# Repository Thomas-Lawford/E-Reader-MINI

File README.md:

Solar Powered E-Reader Keychain 

Has a custom E-Paper driver circuit MicroSD card interface and solar energy harvesting circuit.

Based on the STM32U073 with sub 1 μW operational power consumption.

Has a custom FILEX implementation that supports EXfat and fat32 file systems (Supports SDUC, SDXC and SDHC), 3d printed Case design and a custom EPD lookup table for the 1.22 inch E paper display.

Power consumption is so low this design is battery free with a supercap to store charge for brief current spikes from microSD card reads.
 
 You can select a text file to read, jump to a specific page, and adjust the font size

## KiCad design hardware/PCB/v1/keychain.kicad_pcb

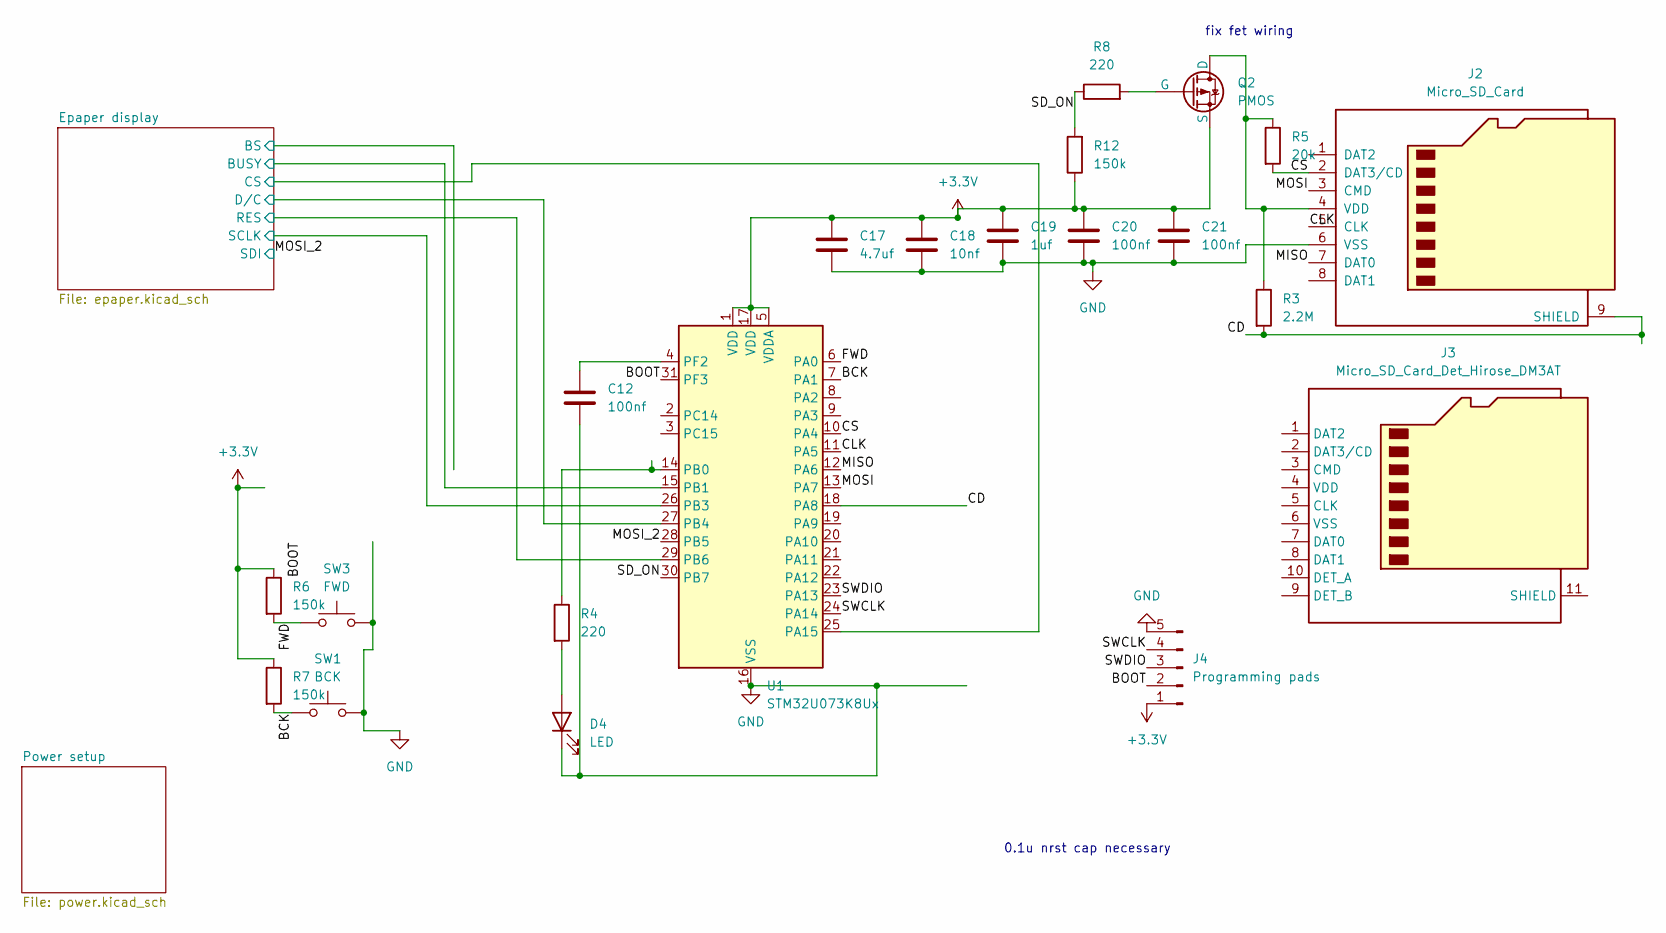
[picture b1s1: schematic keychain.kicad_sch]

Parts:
C12, C20, C21: 100nf; C_0603_1608Metric
C17: 4.7uf; C_0603_1608Metric
C18: 10nf; C_0603_1608Metric
C19: 1uf; C_0603_1608Metric
D4: LED; LED_0805_2012Metric
J2: Micro_SD_Card; CONN9_MSD-4-A_SSD
J3: Micro_SD_Card_Det_Hirose_DM3AT
J4: Programming pads; 4_p_SWD_prog
Q2: PMOS; SOT-23
R3: 2.2M; R_0603_1608Metric
R4, R8: 220; R_0603_1608Metric
R5: 20k; R_0603_1608Metric
R6, R7, R12: 150k; R_0603_1608Metric
SW1: BCK; SW_Tactile_SPST_NO_Straight_CK_PTS636Sx25SMTRLFS
SW3: FWD; SW_Tactile_SPST_NO_Straight_CK_PTS636Sx25SMTRLFS
U1: STM32U073K8Ux; QFN-32-1EP_5x5mm_P0.5mm_EP3.45x3.45mm

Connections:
+3.3V: C17.1, C18.1, C19.1, C20.1, C21.1, J4.1, Q2.3 (S), R6.1, R7.1, R12.1, U1.1 (VDD), U1.5 (VDDA), U1.17 (VDD); also elsewhere on the board
/BCK: R7.2, SW1.1, U1.7 (PA1)
/BOOT: J4.2, U1.31 (PF3)
/CD: J2.9 (SHIELD), R3.2, U1.18 (PA8)
/CLK: J2.5 (CLK), U1.11 (PA5)
/CS: J2.2 (DAT3/CD), R5.2, U1.10 (PA4)
/Epaper display/BUSY: U1.15 (PB1); also elsewhere on the board
/Epaper display/CS: U1.25 (PA15); also elsewhere on the board
/Epaper display/D/C: U1.27 (PB4); also elsewhere on the board
/Epaper display/RES: U1.29 (PB6); also elsewhere on the board
/Epaper display/SCLK: U1.26 (PB3); also elsewhere on the board
/FWD: R6.2, SW3.1, U1.6 (PA0)
/MISO: J2.7 (DAT0), U1.12 (PA6)
/MOSI: J2.3 (CMD), U1.13 (PA7)
/MOSI_2: U1.28 (PB5); also elsewhere on the board
/SD_ON: R8.1, R12.2, U1.30 (PB7)
/SWCLK: J4.4, U1.24 (PA14)
/SWDIO: J4.3, U1.23 (PA13)
GND: C12.2, C17.2, C18.2, C19.2, C20.2, C21.2, D4.1 (K), J2.6 (VSS), J4.5, SW1.2, SW3.2, U1.16 (VSS), U1.32 (VSS), U1.33 (VSS); also elsewhere on the board
unnamed: D4.2 (A), R4.2
unnamed: J2.4 (VDD), Q2.1 (D), R3.1, R5.1
unnamed: Q2.2 (G), R8.2
unnamed: R4.1, U1.14 (PB0)
unnamed: C12.1, U1.4 (PF2)

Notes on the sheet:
fix fet wiring
0.1u nrst cap necessary

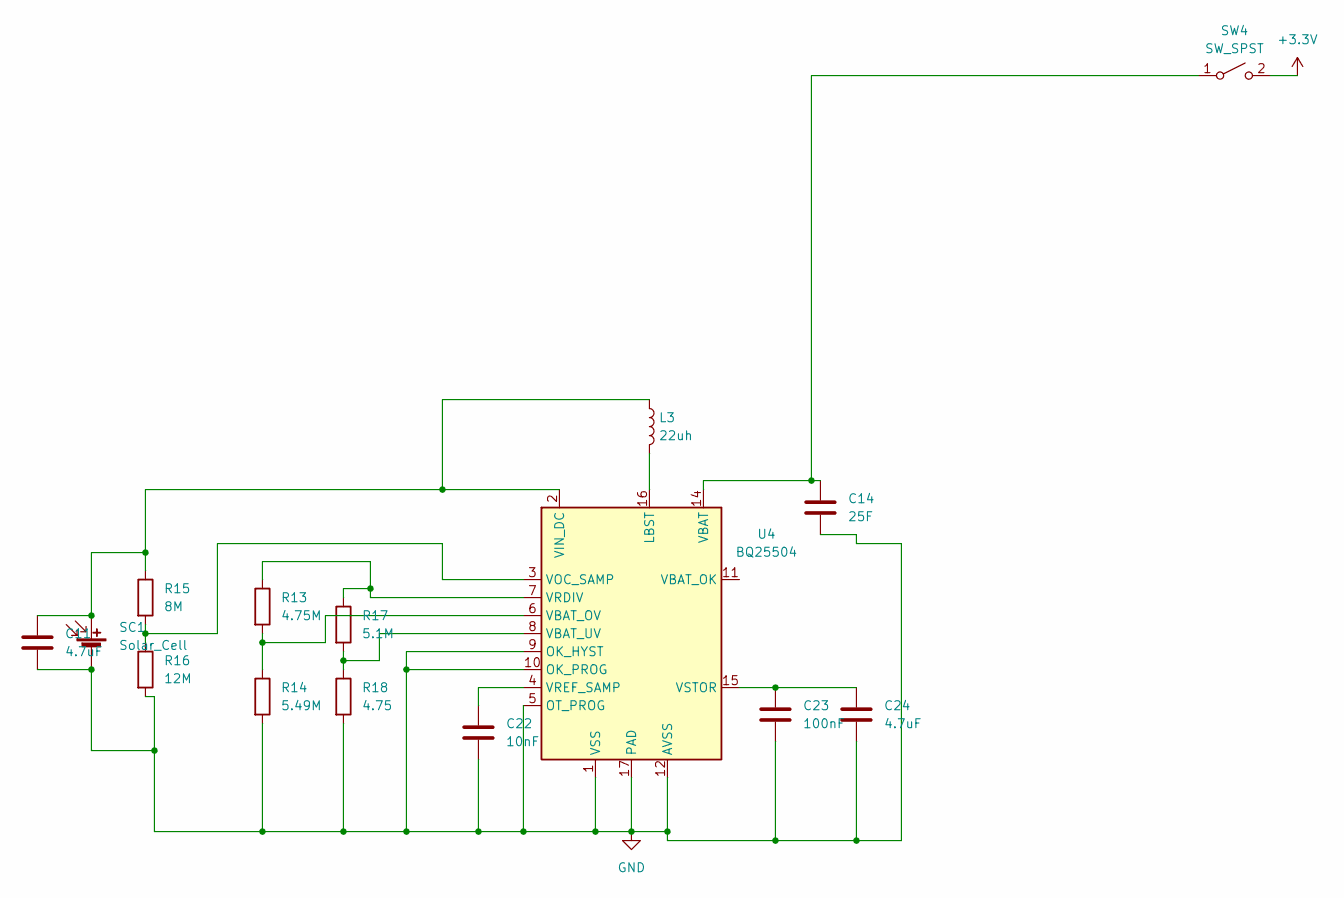
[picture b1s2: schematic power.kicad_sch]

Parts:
C11, C24: 4.7uF; C_0603_1608Metric
C14: 25F; 25F 3.8V cap
C22: 10nF; C_0603_1608Metric
C23: 100nF; C_0603_1608Metric
L3: 22uh; IND_ASPI-0315FS-220M-T2
R13: 4.75M; R_0603_1608Metric
R14: 5.49M; R_0603_1608Metric
R15: 8M; R_0603_1608Metric
R16: 12M; R_0603_1608Metric
R17: 5.1M; R_0603_1608Metric
R18: 4.75; R_0603_1608Metric
SC1: Solar_Cell; 25F 3.8V cap
SW4: SW_SPST; SW_SLW-864574-5A-RA-N-D
U4: BQ25504; VQFN-16-1EP_3x3mm_P0.5mm_EP1.68x1.68mm

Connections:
+3.3V: SW4.2 (B); also elsewhere on the board
GND: C11.2, C14.2, C22.2, C23.2, C24.2, R14.2, R16.2, R18.2, SC1.2 (-), U4.1 (VSS), U4.5 (OT_PROG), U4.9 (OK_HYST), U4.10 (OK_PROG), U4.12 (AVSS), U4.13 (VSS), U4.17 (PAD); also elsewhere on the board
unnamed: C11.1, L3.1, R15.1, SC1.1 (+), U4.2 (VIN_DC)
unnamed: C14.1, SW4.1 (A), U4.14 (VBAT)
unnamed: L3.2, U4.16 (LBST)
unnamed: R13.2, R14.1, U4.6 (VBAT_OV)
unnamed: R17.2, R18.1, U4.8 (VBAT_UV)
unnamed: R15.2, R16.1, U4.3 (VOC_SAMP)
unnamed: R13.1, R17.1, U4.7 (VRDIV)
unnamed: C22.1, U4.4 (VREF_SAMP)
unnamed: C23.1, C24.1, U4.15 (VSTOR)

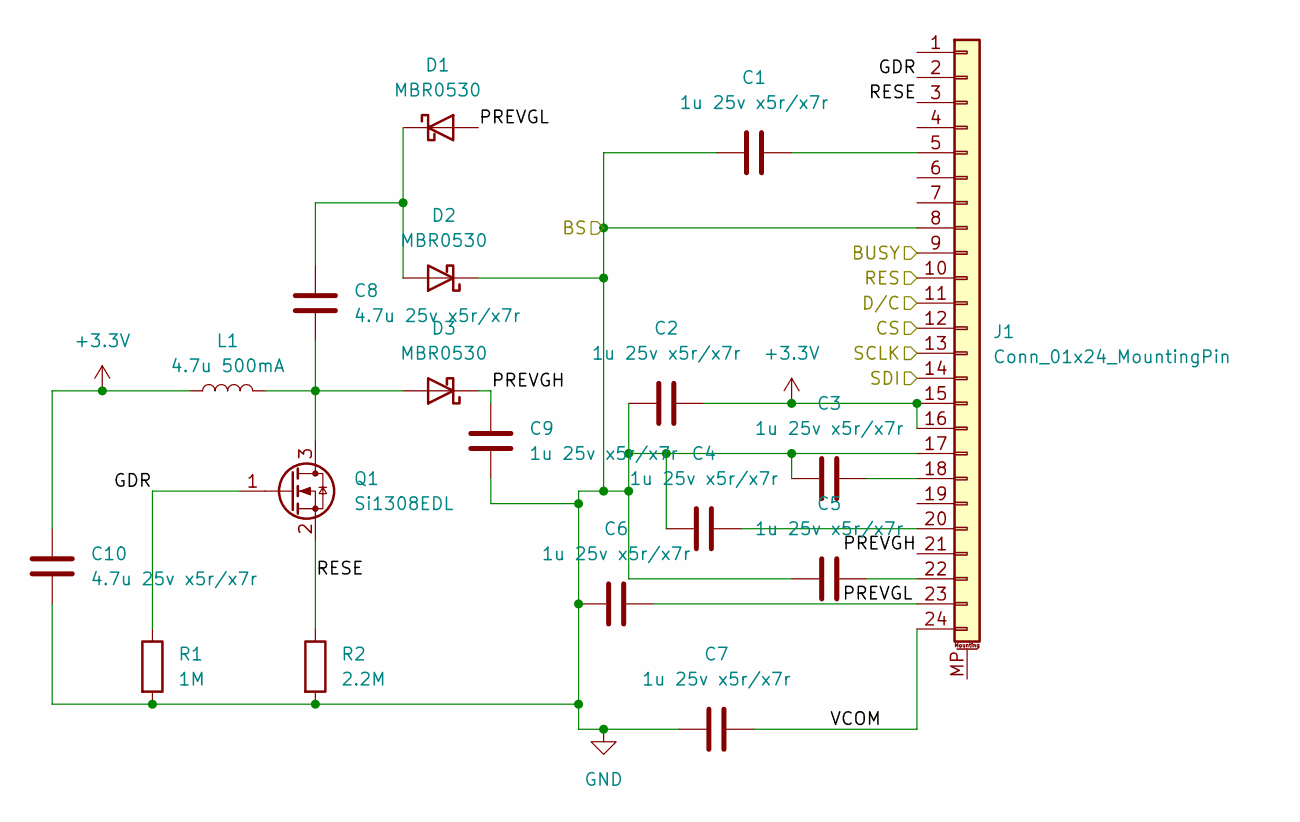
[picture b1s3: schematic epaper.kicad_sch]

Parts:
C1, C2, C3, C4, C5, C6, C7, C9: 1u 25v x5r/x7r; C_0603_1608Metric
C8, C10: 4.7u 25v x5r/x7r; C_0603_1608Metric
D1, D2, D3: MBR0530; D_SOD-123
J1: Conn_01x24_MountingPin; AMPHENOL_F33Z-1A7Q1-E8C24
L1: 4.7u 500mA; L_1008_2520Metric
Q1: Si1308EDL; SOT-323_SC-70
R1: 1M; R_0603_1608Metric
R2: 2.2M; R_0603_1608Metric

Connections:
+3.3V: C2.2, C10.2, J1.15, J1.16, L1.1; also elsewhere on the board
/Epaper display/BUSY: J1.9; also elsewhere on the board
/Epaper display/CS: J1.12; also elsewhere on the board
/Epaper display/D/C: J1.11; also elsewhere on the board
/Epaper display/GDR: J1.2, Q1.1 (G), R1.1
/Epaper display/PREVGH: C9.2, D3.1 (K), J1.21
/Epaper display/PREVGL: C6.2, D1.2 (A), J1.23
/Epaper display/RES: J1.10; also elsewhere on the board
/Epaper display/RESE: J1.3, Q1.2 (S), R2.1
/Epaper display/SCLK: J1.13; also elsewhere on the board
/Epaper display/VCOM: C7.2, J1.24
/MOSI_2: J1.14; also elsewhere on the board
GND: C1.1, C2.1, C3.1, C4.1, C5.1, C6.1, C7.1, C9.1, C10.1, D2.1 (K), J1.8, J1.17, R1.2, R2.2; also elsewhere on the board
unnamed: C8.1, D1.1 (K), D2.2 (A)
unnamed: C8.2, D3.2 (A), L1.2, Q1.3 (D)
unnamed: C1.2, J1.5
unnamed: C3.2, J1.18
unnamed: C4.2, J1.20
unnamed: C5.2, J1.22

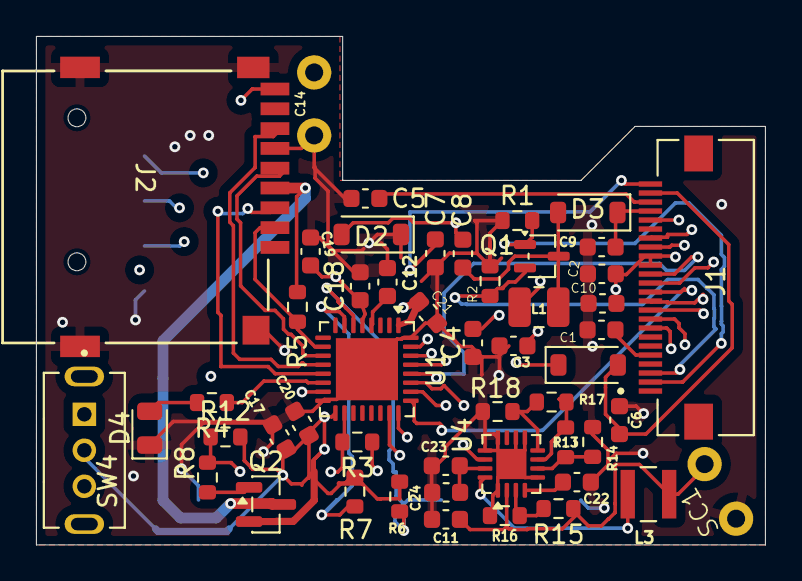
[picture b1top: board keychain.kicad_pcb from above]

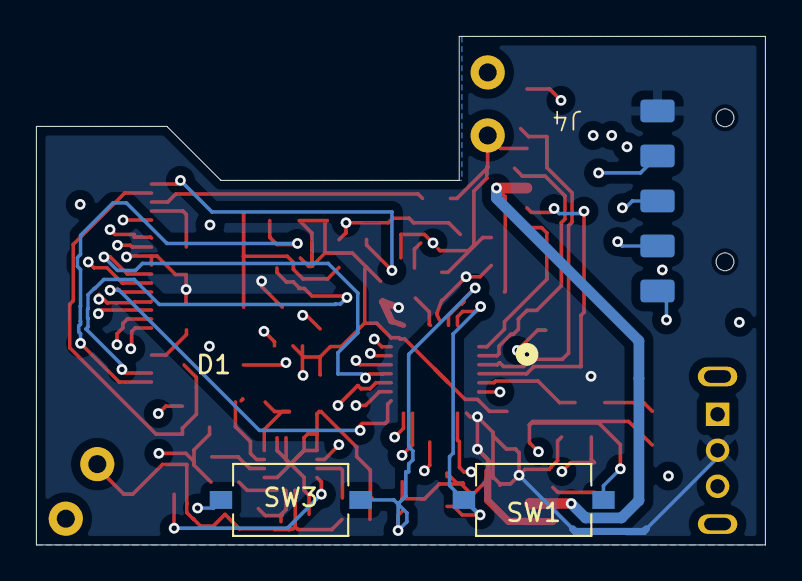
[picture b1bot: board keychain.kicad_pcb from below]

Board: 4 copper layers, 40.5 x 28.2 mm, 53 parts (3 on the bottom side), 44 nets.

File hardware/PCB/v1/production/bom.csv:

Designator,Footprint,Quantity,Value,LCSC Part #
"C1, C2, C3, C4, C5, C6, C7, C9",0603,8,1u 25v x5r/x7r,
"C10, C8",0603,2,4.7u 25v x5r/x7r,
"C11, C17, C24",0603,3,4.7uF,
"C12, C20, C21, C23",0603,4,100nf,
C14,25F 3.8V cap,1,25F,
"C18, C22",0603,2,10nf,
C19,0603,1,1uf,
"D1, D2, D3",D_SOD-123,3,MBR0530,
D4,0805,1,LED,
J1,AMPHENOL_F33Z-1A7Q1-E8C24,1,Conn_01x24_MountingPin,
J2,CONN9_MSD-4-A_SSD,1,Micro_SD_Card,
J4,4_p_SWD_prog,1,Programming pads,
L1,1008,1,4.7u 500mA,
L3,IND_ASPI-0315FS-220M-T2,1,22uh,
Q1,SOT-323_SC-70,1,Si1308EDL,
Q2,SOT-23,1,PMOS,
R1,0603,1,1M,
"R12, R6, R7",0603,3,150k,
R13,0603,1,4.75M,
R14,0603,1,5.49M,
R15,0603,1,8M,
R16,0603,1,12M,
R17,0603,1,5.1M,
R18,0603,1,4.75,
"R2, R3",0603,2,2.2M,
"R4, R8",0603,2,220,
R5,0603,1,20k,
SC1,25F 3.8V cap,1,Solar_Cell,
SW1,SW_Tactile_SPST_NO_Straight_CK_PTS636Sx25SMTRLFS,1,BCK,
SW3,SW_Tactile_SPST_NO_Straight_CK_PTS636Sx25SMTRLFS,1,FWD,
SW4,SW_SLW-864574-5A-RA-N-D,1,SW_SPST,
U1,QFN-32-1EP_5x5mm_P0.5mm_EP3.45x3.45mm,1,STM32U073K8Ux,
U4,VQFN-16-1EP_3x3mm_P0.5mm_EP1.68x1.68mm,1,BQ25504,

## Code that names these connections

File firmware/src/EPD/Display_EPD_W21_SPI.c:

#include "Display_EPD_W21_spi.h"

//E-paper GPIO initialization
void EPD_GPIO_Init(void)
{
	    GPIO_InitTypeDef GPIO_InitStruct = {0};

    __HAL_RCC_GPIOA_CLK_ENABLE();
    __HAL_RCC_GPIOB_CLK_ENABLE();

    // CS (PA15), output
    GPIO_InitStruct.Pin = GPIO_PIN_15;
    GPIO_InitStruct.Mode = GPIO_MODE_OUTPUT_PP;
    GPIO_InitStruct.Pull = GPIO_NOPULL;
    GPIO_InitStruct.Speed = GPIO_SPEED_FREQ_LOW;
    HAL_GPIO_Init(GPIOA, &GPIO_InitStruct);

    // MOSI (PB5), CLK (PB3), DC (PB4), RST (PB6), output
    GPIO_InitStruct.Pin = GPIO_PIN_3 | GPIO_PIN_4 | GPIO_PIN_5 | GPIO_PIN_6;
    HAL_GPIO_Init(GPIOB, &GPIO_InitStruct);

    // BUSY (PB1), input with pull-up
    GPIO_InitStruct.Pin = GPIO_PIN_1;
    GPIO_InitStruct.Mode = GPIO_MODE_INPUT;
    GPIO_InitStruct.Pull = GPIO_PULLUP;
    HAL_GPIO_Init(GPIOB, &GPIO_InitStruct); //make sure configured in cubemx
}



//SPI write byte
void SPI_Write(unsigned char value)
{
	unsigned char i;
  EPD_W21_CLK_0;
	for(i=0;i<8;i++)
	{
		if(value&0x80)
		  EPD_W21_MOSI_1 ;
		else
		  EPD_W21_MOSI_0 ;
		EPD_W21_CLK_1;
	  EPD_W21_CLK_0;
		value=value<<1;
  }
}

//SPI write command
void EPD_W21_WriteCMD(unsigned char command)
{
	EPD_W21_CS_0;
	EPD_W21_DC_0;  // D/C#   0:command  1:data
	SPI_Write(command);
	EPD_W21_CS_1;
}
//SPI write data
void EPD_W21_WriteDATA(unsigned char datas)
{
	EPD_W21_CS_0;
	EPD_W21_DC_1;  // D/C#   0:command  1:data
	SPI_Write(datas);
	EPD_W21_CS_1;
}

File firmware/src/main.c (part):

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static void MX_RTC_Init(void);
/* USER CODE BEGIN PFP */
/* Configure Wakeup pins */
/* FWD_Pin = PWR_WAKEUP_PIN1 (PA0) - falling edge (high to low) */
static void PVD_Config(void);
static void enter_standby(uint8_t high);
static void Configure_RTC_WakeupTimer(uint32_t seconds);
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      //memset((void *)retained_string, 0, sizeof(retained_string));
      WRITE_REG(TAMP->BKP8R, 3);
      g_result=MX_FileX_GetTextFiles(filenames, &file_count);
      HAL_GPIO_WritePin(GPIOB, SD_ON_Pin, GPIO_PIN_SET);
   }
   uint32_t sr1 = READ_REG(PWR->SR1);  /* read before clearing */
   WRITE_REG(PWR->SCR, PWR_SCR_CWUF1 | PWR_SCR_CWUF3 | PWR_SCR_CSBF);
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   if (!first_boot){

	   //int negtive=0;
       if ((sr1 & PWR_SR1_WUF1)==PWR_SR1_WUF1){//if fwd increment stuff   //HAL_GPIO_WritePin(GPIOB, GPIO_PIN_0, GPIO_PIN_SET);
    	  if(!settings){
    		  if(menu==2){
    			  temp=temp+1;
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          HAL_PWREx_DisableLowPowerRunMode();
          SystemClock_Config_Normal();
          g_result=FX_SUCCESS;}
          //HAL_GPIO_WritePin(GPIOB, SD_ON_Pin, GPIO_PIN_SET);
          //SystemClock_Config_LowPower();
          //HAL_PWREx_EnableLowPowerRunMode();
          //HAL_Delay(300);
          //HAL_PWREx_DisableLowPowerRunMode();
          //SystemClock_Config_Normal();
        	if(HAL_GPIO_ReadPin(FWD_GPIO_Port, FWD_Pin) == GPIO_PIN_RESET){
        		menu=0;
        		if(!settings){//enter book
        			//HAL_GPIO_WritePin(GPIOB, GPIO_PIN_0, GPIO_PIN_SET);
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        			page=page*10+num;
        		}
        	}//fwd double press
        	if(HAL_GPIO_ReadPin(BCK_GPIO_Port, BCK_Pin) == GPIO_PIN_RESET){
        		menu=0;
        		if(!settings){//enter settings first time
	      	      	temp=temp+1;
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	          HAL_PWREx_DisableLowPowerRunMode();
	          SystemClock_Config_Normal();
	          g_result=FX_SUCCESS;
        	if(HAL_GPIO_ReadPin(FWD_GPIO_Port, FWD_Pin) == GPIO_PIN_RESET){

				fontsize=fontsize+1;
				up=1;
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					fontsize=4;
        	}
        	}
        	if(HAL_GPIO_ReadPin(BCK_GPIO_Port, BCK_Pin) == GPIO_PIN_RESET){
        		if(!exits){
        	    if (fontsize>0){fontsize=fontsize-1;}
        	    down=1;}
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  HAL_GPIO_WritePin(SD_CS_GPIO_Port, SD_CS_Pin, GPIO_PIN_SET);

  /*Configure GPIO pin Output Level */
  HAL_GPIO_WritePin(GPIOB, DEBUG_LED_Pin|EPD_DC_Pin|EPD_RES_Pin|SD_ON_Pin, GPIO_PIN_RESET);

  /*Configure GPIO pin : SD_CS_Pin */
  GPIO_InitStruct.Pin = SD_CS_Pin;
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  GPIO_InitStruct.Speed = GPIO_SPEED_FREQ_LOW;
  HAL_GPIO_Init(SD_CS_GPIO_Port, &GPIO_InitStruct);

  /*Configure GPIO pins : DEBUG_LED_Pin EPD_DC_Pin EPD_RES_Pin SD_ON_Pin */
  GPIO_InitStruct.Pin = DEBUG_LED_Pin|EPD_DC_Pin|EPD_RES_Pin|SD_ON_Pin;
  GPIO_InitStruct.Mode = GPIO_MODE_OUTPUT_PP;
  GPIO_InitStruct.Pull = GPIO_NOPULL;
  GPIO_InitStruct.Speed = GPIO_SPEED_FREQ_LOW;
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  GPIO_InitStruct.Speed = GPIO_SPEED_FREQ_LOW;
  GPIO_InitStruct.Alternate = GPIO_AF5_SPI1;
  HAL_GPIO_Init(GPIOA, &GPIO_InitStruct);*/
  GPIO_InitStruct.Pin  = FWD_Pin;
  GPIO_InitStruct.Mode = GPIO_MODE_INPUT;  // plain input, no EXTI
  GPIO_InitStruct.Pull = GPIO_NOPULL;      // you have external pull-ups
  HAL_GPIO_Init(FWD_GPIO_Port, &GPIO_InitStruct);
  GPIO_InitStruct.Pin  = BCK_Pin;
  GPIO_InitStruct.Mode = GPIO_MODE_INPUT;  // plain input, no EXTI
  GPIO_InitStruct.Pull = GPIO_NOPULL;      // you have external pull-ups
  HAL_GPIO_Init(FWD_GPIO_Port, &GPIO_InitStruct);
  /* USER CODE END MX_GPIO_Init_2 */
}

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
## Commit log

2026-06-09 added firmware files
2026-06-09 uploaded images of finished project
2026-06-09 added images and better description
    Added functionality details for text file reading and font size adjustment.
2026-06-09 Added hardware related files
    Added case 3d model, PCB files and parts
2026-06-13 added screenshot of most recent PCB design
2026-06-13 Add PCB design image to README
2026-06-13 Fix image link formatting in README.md

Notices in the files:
firmware/src/main.c:
Copyright (c) 2026 STMicroelectronics.
All rights reserved.
This software is licensed under terms that can be found in the LICENSE file
